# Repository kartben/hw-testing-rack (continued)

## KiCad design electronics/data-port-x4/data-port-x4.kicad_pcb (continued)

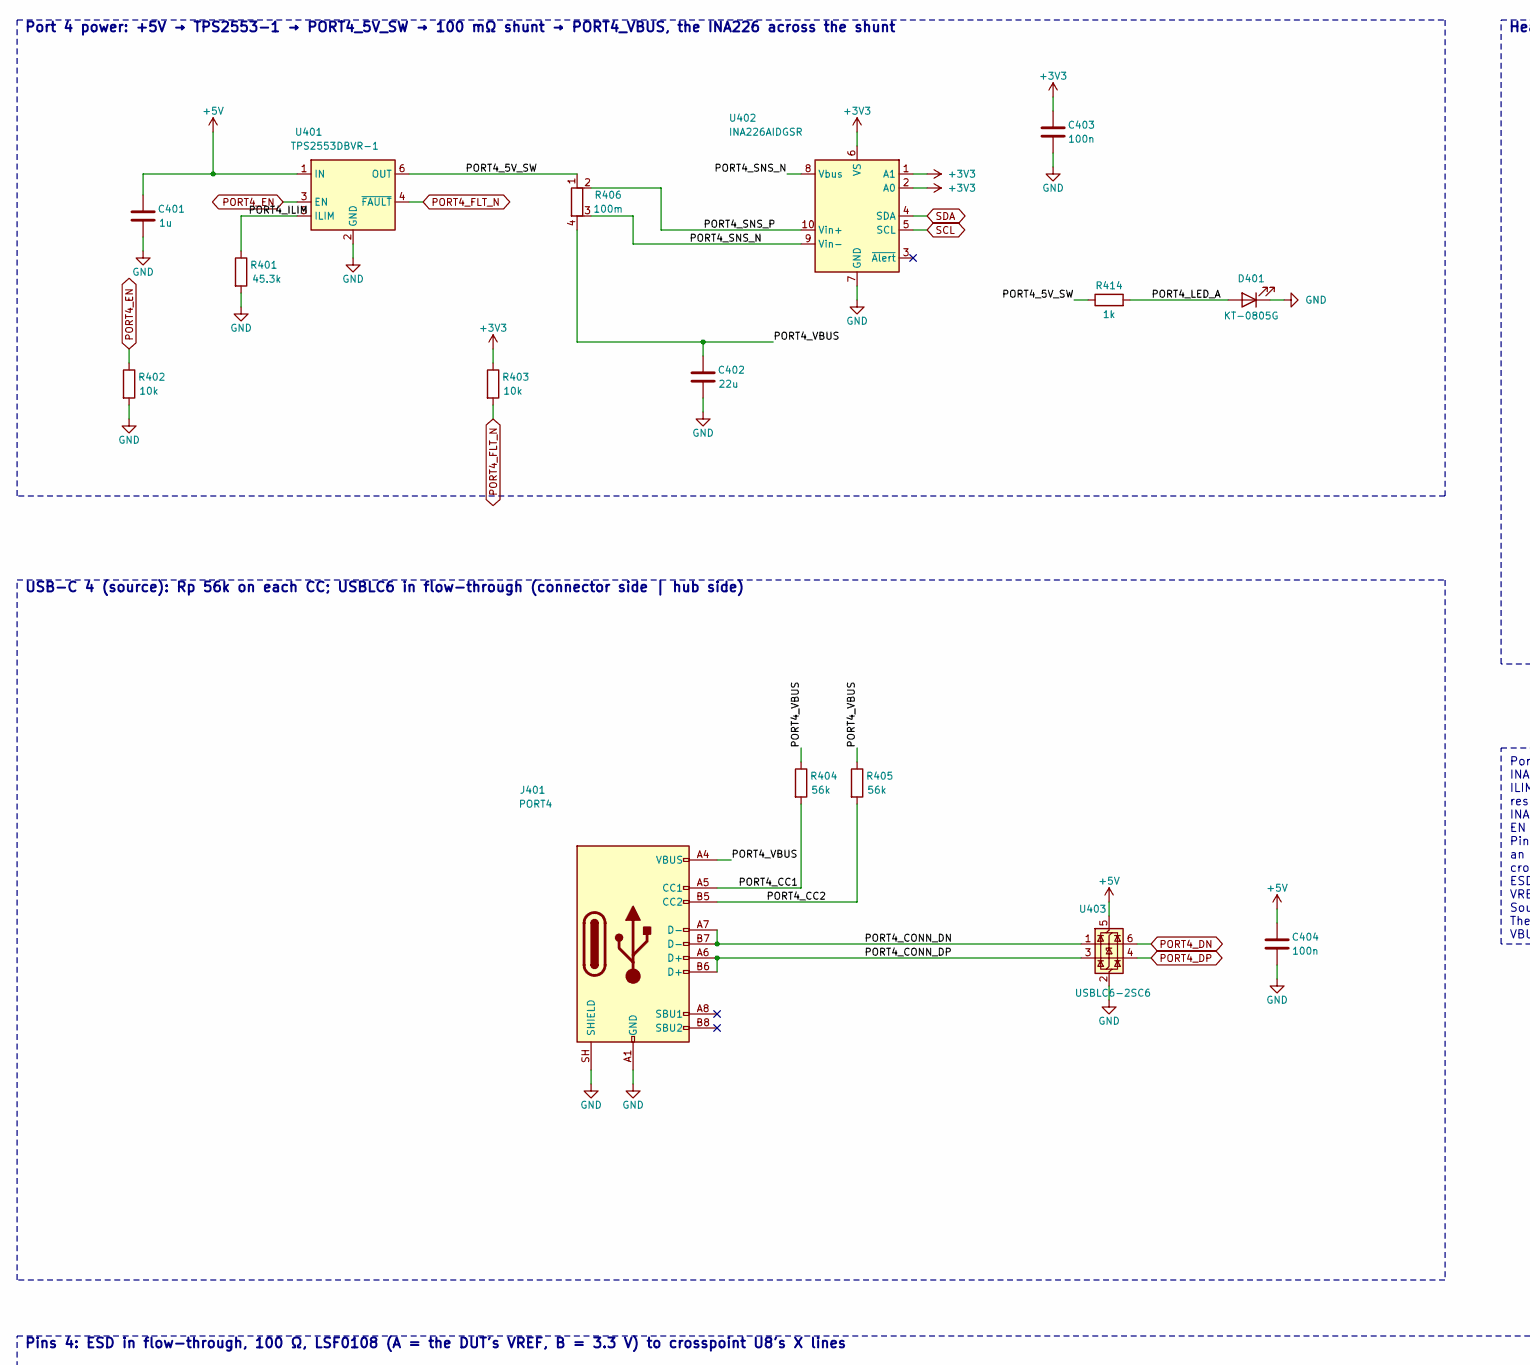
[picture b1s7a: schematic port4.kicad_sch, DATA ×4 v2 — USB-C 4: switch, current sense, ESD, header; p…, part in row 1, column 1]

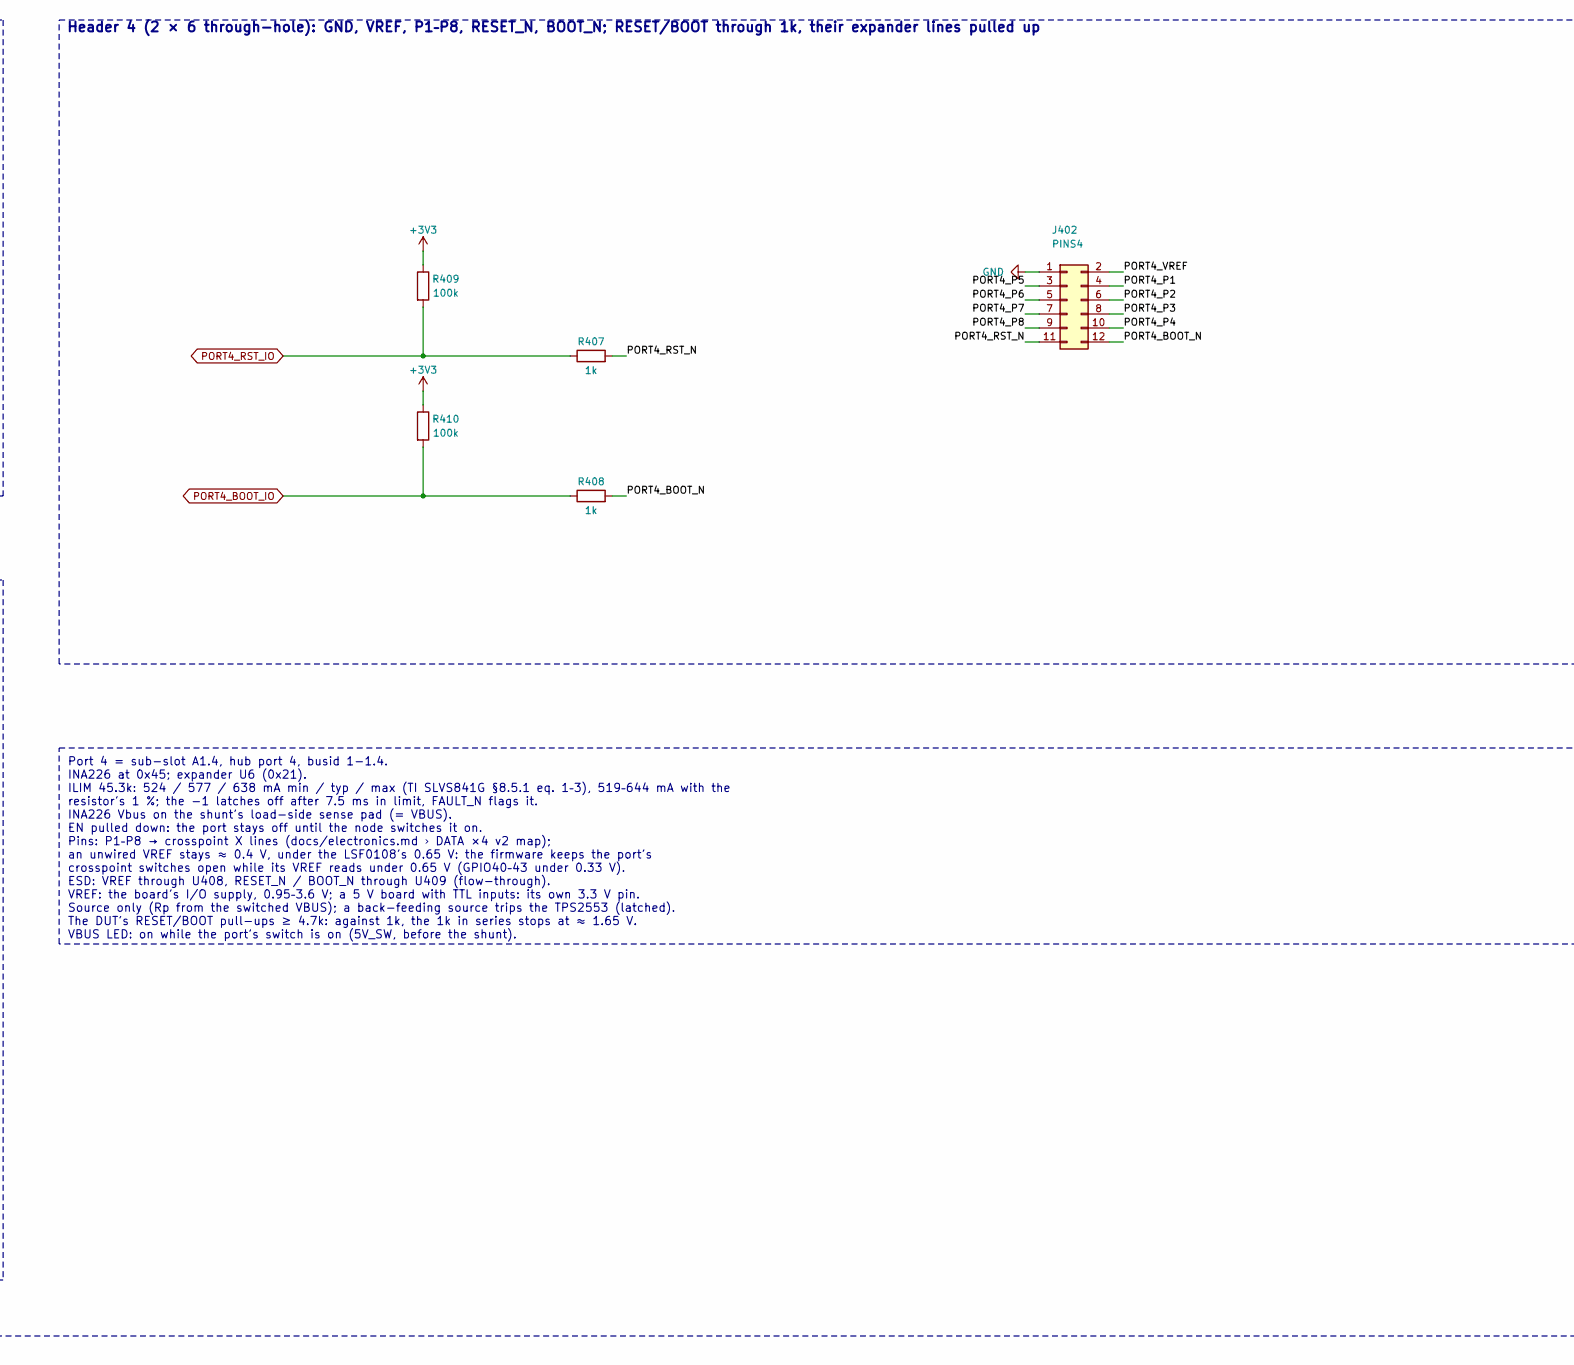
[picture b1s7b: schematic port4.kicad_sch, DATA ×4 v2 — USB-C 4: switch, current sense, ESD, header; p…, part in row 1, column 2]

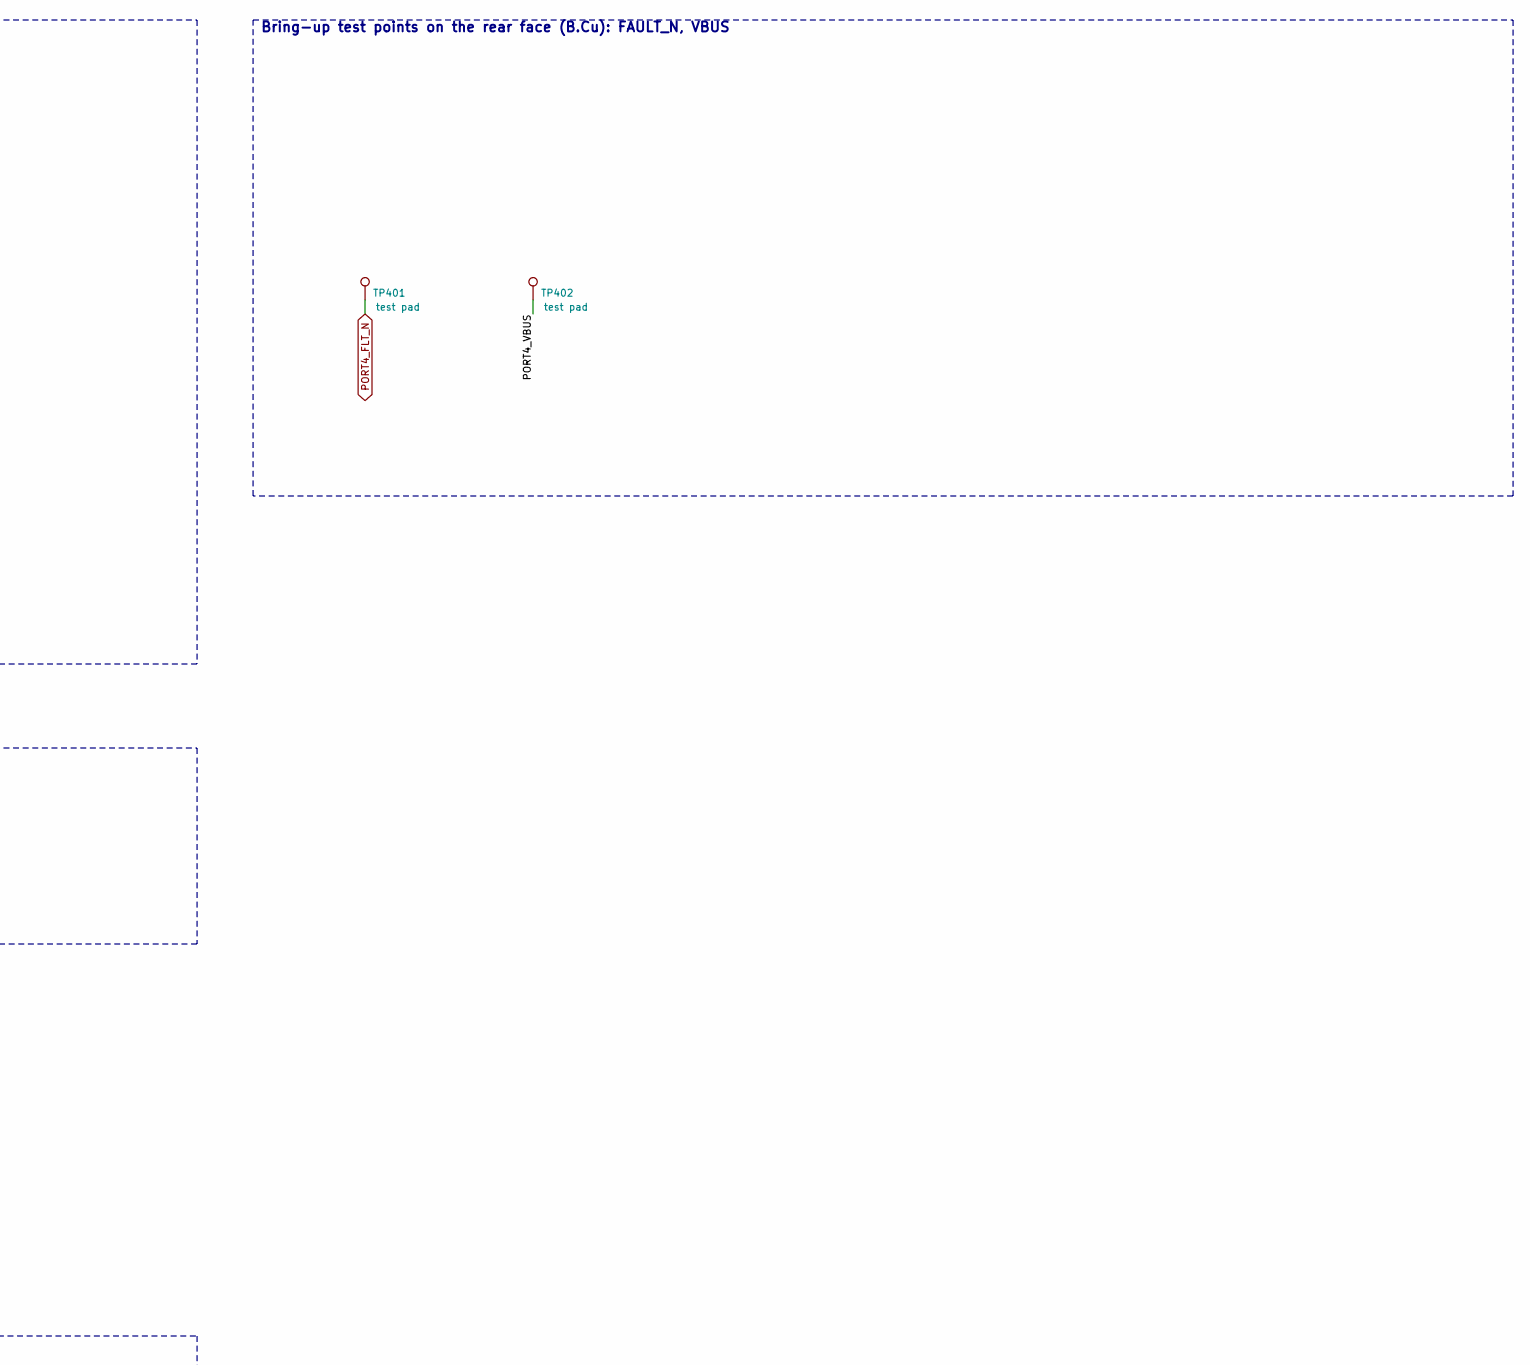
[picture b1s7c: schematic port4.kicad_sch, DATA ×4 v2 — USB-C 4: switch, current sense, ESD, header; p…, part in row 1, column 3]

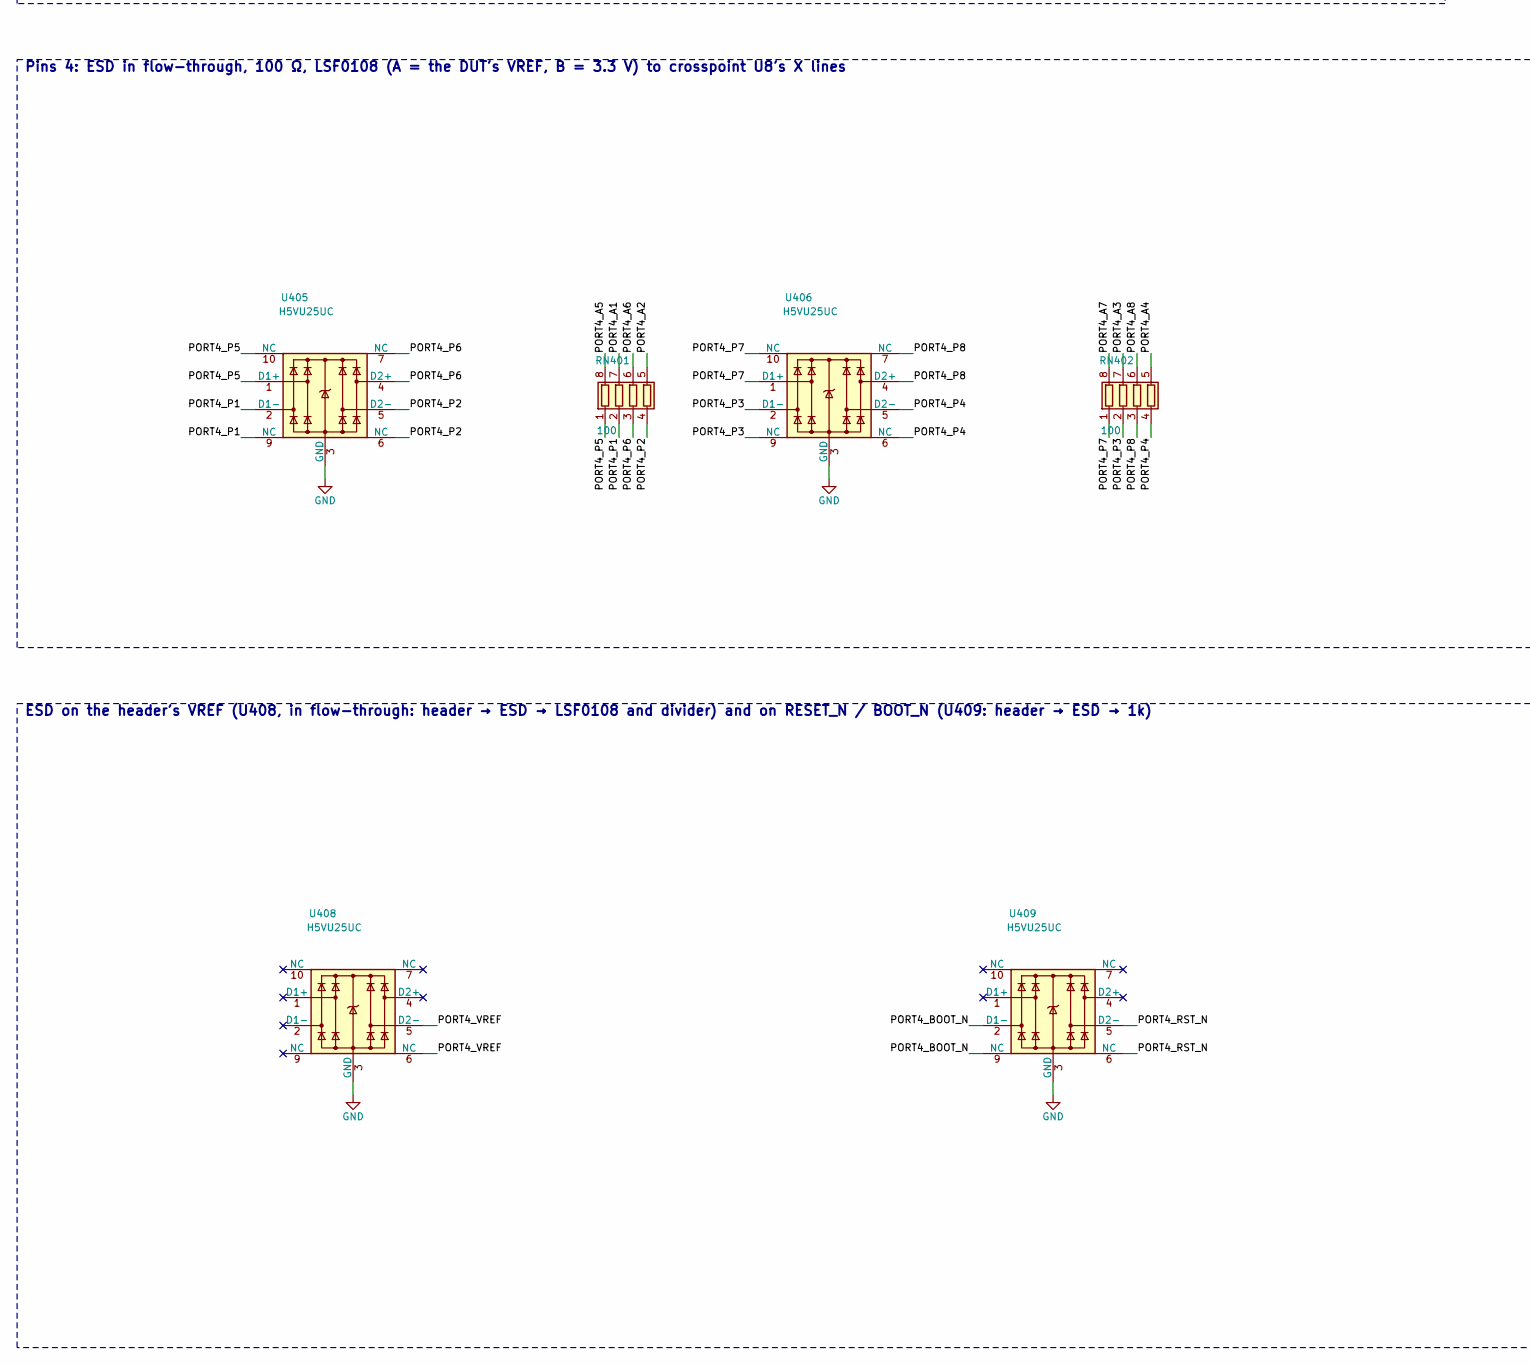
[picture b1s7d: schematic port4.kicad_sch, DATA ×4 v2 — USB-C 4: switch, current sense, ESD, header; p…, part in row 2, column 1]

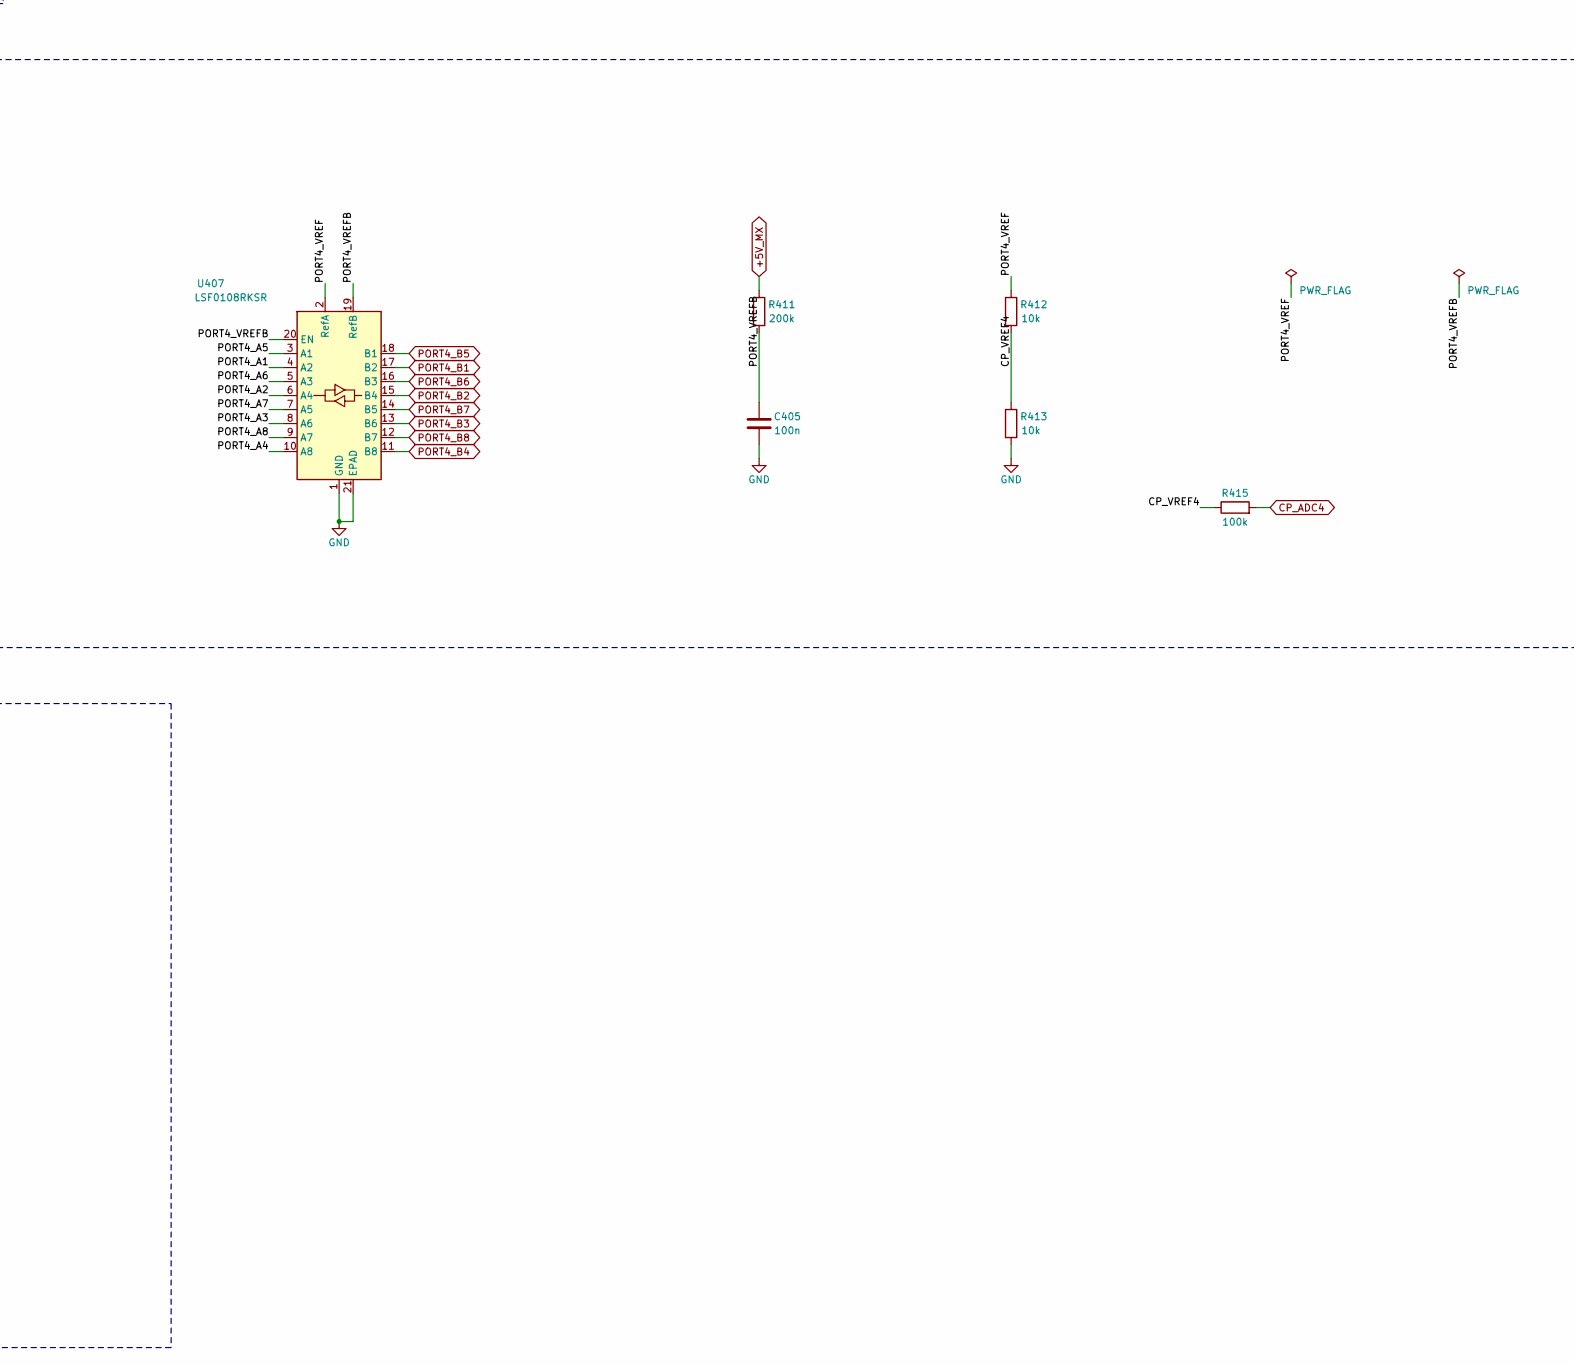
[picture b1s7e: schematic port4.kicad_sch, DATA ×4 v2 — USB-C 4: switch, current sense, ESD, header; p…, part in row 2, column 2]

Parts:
C401: 1u; C_0402_1005Metric; MPN CL05A105KA5NQNC; LCSC C52923
C402: 22u; C_0805_2012Metric; MPN CL21A226MAQNNNE; LCSC C45783
C403, C404, C405: 100n; C_0402_1005Metric; MPN CL05B104KO5NNNC; LCSC C1525
D401: KT-0805G; LED_0805_2012Metric; MPN KT-0805G; LCSC C2297
J401: PORT4; USB_C_Receptacle_GCT_USB4145-03-0170-C_Vertical; MPN USB4145-03-0170-C; LCSC C5181332
J402: PINS4; PinHeader_2x06_P2.54mm_Vertical; MPN HX PZ2.54-2x6P ZZ; LCSC C32713279
R401: 45.3k; R_0402_1005Metric; MPN FRC0402F4532TS; LCSC C2933099
R402, R403, R412, R413: 10k; R_0402_1005Metric; MPN 0402WGF1002TCE; LCSC C25744
R404, R405: 56k; R_0402_1005Metric; MPN 0402WGF5602TCE; LCSC C25796
R406: 100m; R_1206_3216Metric_Kelvin; MPN 1206W4F100LT5E; LCSC C25334
R407, R408, R414: 1k; R_0402_1005Metric; MPN 0402WGF1001TCE; LCSC C11702
R409, R410, R415: 100k; R_0402_1005Metric; MPN 0402WGF1003TCE; LCSC C25741
R411: 200k; R_0402_1005Metric; MPN 0402WGF2003TCE; LCSC C25764
RN401, RN402: 100; R_Array_Convex_4x0402; MPN 4D02WGJ0101TCE; LCSC C48442
TP401: test pad; TestPoint_Pad_D1.0mm; MPN test pad
TP402: test pad; TestPoint_Pad_D1.5mm; MPN test pad
U401: TPS2553DBVR-1; SOT-23-6; MPN TPS2553DBVR-1; LCSC C111738
U402: INA226AIDGSR; TSSOP-10_3x3mm_P0.5mm; MPN INA226AIDGSR; LCSC C49851
U403: USBLC6-2SC6; SOT-23-6; MPN USBLC6-2SC6; LCSC C7519
U405, U406, U408, U409: H5VU25UC; DFN2510-10L_2.5x1.0mm_P0.5mm; MPN H5VU25UC; LCSC C20615800
U407: LSF0108RKSR; DHVQFN-20-1EP_2.5x4.5mm_P0.5mm_EP1x3mm; MPN LSF0108RKSR; LCSC C130008

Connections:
+3V3: C403.1, R403.1, R409.1, R410.1, U402.1 (A1), U402.2 (A0), U402.6 (VS); also elsewhere on the board
+5V: C401.1, C404.1, U401.1 (IN), U403.5 (VBUS); also elsewhere on the board
+5V_MX: R411.1; also elsewhere on the board
/Port 4/CP_VREF4: R412.2, R413.1, R415.1
/Port 4/PORT4_5V_SW: R406.1, R414.1, U401.6 (OUT)
/Port 4/PORT4_A1: RN401.7 (R2.2), U407.4 (A2)
/Port 4/PORT4_A2: RN401.5 (R4.2), U407.6 (A4)
/Port 4/PORT4_A3: RN402.7 (R2.2), U407.8 (A6)
/Port 4/PORT4_A4: RN402.5 (R4.2), U407.10 (A8)
/Port 4/PORT4_A5: RN401.8 (R1.2), U407.3 (A1)
/Port 4/PORT4_A6: RN401.6 (R3.2), U407.5 (A3)
/Port 4/PORT4_A7: RN402.8 (R1.2), U407.7 (A5)
/Port 4/PORT4_A8: RN402.6 (R3.2), U407.9 (A7)
/Port 4/PORT4_BOOT_N: J402.12, R408.2, U409.2 (D1-), U409.9 (NC)
/Port 4/PORT4_CC1: J401.A5 (CC1), R404.2
/Port 4/PORT4_CC2: J401.B5 (CC2), R405.2
/Port 4/PORT4_CONN_DN: J401.A7 (D-), J401.B7 (D-), U403.1 (I/O1)
/Port 4/PORT4_CONN_DP: J401.A6 (D+), J401.B6 (D+), U403.3 (I/O2)
/Port 4/PORT4_ILIM: R401.1, U401.5 (ILIM)
/Port 4/PORT4_LED_A: D401.2 (A), R414.2
/Port 4/PORT4_P1: J402.4, RN401.2 (R2.1), U405.2 (D1-), U405.9 (NC)
/Port 4/PORT4_P2: J402.6, RN401.4 (R4.1), U405.5 (D2-), U405.6 (NC)
/Port 4/PORT4_P3: J402.8, RN402.2 (R2.1), U406.2 (D1-), U406.9 (NC)
/Port 4/PORT4_P4: J402.10, RN402.4 (R4.1), U406.5 (D2-), U406.6 (NC)
/Port 4/PORT4_P5: J402.3, RN401.1 (R1.1), U405.1 (D1+), U405.10 (NC)
/Port 4/PORT4_P6: J402.5, RN401.3 (R3.1), U405.4 (D2+), U405.7 (NC)
/Port 4/PORT4_P7: J402.7, RN402.1 (R1.1), U406.1 (D1+), U406.10 (NC)
/Port 4/PORT4_P8: J402.9, RN402.3 (R3.1), U406.4 (D2+), U406.7 (NC)
/Port 4/PORT4_RST_N: J402.11, R407.2, U409.5 (D2-), U409.6 (NC)
/Port 4/PORT4_SNS_N: R406.3, U402.8 (Vbus), U402.9 (Vin-)
/Port 4/PORT4_SNS_P: R406.2, U402.10 (Vin+)
/Port 4/PORT4_VBUS: C402.1, J401.A4 (VBUS), J401.A9 (VBUS), J401.B4 (VBUS), J401.B9 (VBUS), R404.1, R405.1, R406.4, TP402.1
/Port 4/PORT4_VREF: J402.2, R412.1, U407.2 (RefA), U408.5 (D2-), U408.6 (NC)
/Port 4/PORT4_VREFB: C405.1, R411.2, U407.19 (RefB), U407.20 (EN)
CP_ADC4: R415.2; also elsewhere on the board
GND: C401.2, C402.2, C403.2, C404.2, C405.2, D401.1 (K), J401.A1 (GND), J401.A12 (GND), J401.B1 (GND), J401.B12 (GND), J401.SH (SHIELD), J402.1, R401.2, R402.2, R413.2, U401.2 (GND), U402.7 (GND), U403.2 (GND), U405.3 (GND), U405.8 (GND), U406.3 (GND), U406.8 (GND), U407.1 (GND), U407.21 (EPAD), U408.3 (GND), U408.8 (GND), U409.3 (GND), U409.8 (GND); also elsewhere on the board
PORT4_B1: U407.17 (B2); also elsewhere on the board
PORT4_B2: U407.15 (B4); also elsewhere on the board
PORT4_B3: U407.13 (B6); also elsewhere on the board
PORT4_B4: U407.11 (B8); also elsewhere on the board
PORT4_B5: U407.18 (B1); also elsewhere on the board
PORT4_B6: U407.16 (B3); also elsewhere on the board
PORT4_B7: U407.14 (B5); also elsewhere on the board
PORT4_B8: U407.12 (B7); also elsewhere on the board
PORT4_BOOT_IO: R408.1, R410.2; also elsewhere on the board
PORT4_DN: U403.6 (I/O1); also elsewhere on the board
PORT4_DP: U403.4 (I/O2); also elsewhere on the board
PORT4_EN: R402.1, U401.3 (EN); also elsewhere on the board
PORT4_FLT_N: R403.2, TP401.1, U401.4 (~FAULT); also elsewhere on the board
PORT4_RST_IO: R407.1, R409.2; also elsewhere on the board
SCL: U402.5 (SCL); also elsewhere on the board
SDA: U402.4 (SDA); also elsewhere on the board

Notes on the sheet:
Port 4 power: +5V → TPS2553-1 → PORT4_5V_SW → 100 mΩ shunt → PORT4_VBUS, the INA226 across the shunt
Bring-up test points on the rear face (B.Cu): FAULT_N, VBUS
USB-C 4 (source): Rp 56k on each CC; USBLC6 in flow-through (connector side | hub side)
Header 4 (2 × 6 through-hole): GND, VREF, P1–P8, RESET_N, BOOT_N; RESET/BOOT through 1k, their expander lines pulled up
ESD on the header's VREF (U408, in flow-through: header → ESD → LSF0108 and divider) and on RESET_N / BOOT_N (U409: header → ESD → 1k)
Pins 4: ESD in flow-through, 100 Ω, LSF0108 (A = the DUT's VREF, B = 3.3 V) to crosspoint U8's X lines
Port 4 = sub-slot A1.4, hub port 4, busid 1-1.4. INA226 at 0x45; expander U6 (0x21). ILIM 45.3k: 524 / 577 / 638 mA min / typ / max (TI SLVS841G §8.5.1 eq. 1–3), 519–644 mA with the resistor's 1 %; the -1 latches off after 7.5 ms in limit, FAULT_N flags it. INA226 Vbus on the shunt's load-side sens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

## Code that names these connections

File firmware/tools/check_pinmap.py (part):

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        "dts": ["bay_node_procpu.dts", "bay_node.dtsi", "bay_node-pinctrl.dtsi"],
        "nets": {
            "BOOT": ("gpio", "gpios"),
            "PC_DET": ("gpio", "pc-detect-gpios"),
            "SVC": ("gpio", "service-gpios"),
            "DUT_EN": ("gpio", "enable-gpios"),
            "DUT_FLT_N": ("gpio", "fault-gpios"),
            "MUX_FORCE_PC": ("gpio", "force-pc-gpios"),
            "AUX_RST_CTL": ("gpio", "reset-gpios"),
            "AUX_BOOT_CTL": ("gpio", "boot-gpios"),
            "INA_ALERT_N": ("gpio", "alert-gpios"),
            "I2C_SDA": ("pinmux", "I2C0_SDA"),
            "I2C_SCL": ("pinmux", "I2C0_SCL"),
            "LED_DIN": ("pinmux", "RMT_OUT0"),
            "AUX_TX": ("pinmux", "UART1_TX"),
            "AUX_RX": ("pinmux", "UART1_RX"),
            "U0TX": ("pinmux", "UART0_TX"),
            "U0RX": ("pinmux", "UART0_RX"),
            "CAN_TXD": ("pinmux", "TWAI_TX"),
            "CAN_RXD": ("pinmux", "TWAI_RX"),
            "POS_IN": ("gpio", "pos-in-gpios"),
            "POS_OUT": ("gpio", "pos-out-gpios"),
            "CAM_SCK": ("pinmux", "SPIM2_SCLK"),
            "CAM_MOSI": ("pinmux", "SPIM2_MOSI"),
            "CAM_MISO": ("pinmux", "SPIM2_MISO"),
            "CAM_CS": ("gpio", "cs-gpios"),
            "CAM_LED": ("pinmux", "LEDC_CH0"),
        },
        # Nets that also appear a second way
        "also": {"AUX_TX": [("gpio", "tx-gpios")]},  # dut-port: the TX pin as a GPIO
        # Nets on fixed-function pins: nothing to check in the devicetree
        "fixed": {"ESP_DN", "ESP_DP"},  # IO19/IO20, the internal USB PHY (&usb_otg)
        # Nets wired on the board that no devicetree node uses yet (README says so): skipped
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            "BOOT": ("gpio", "gpios", "boot_button"),
            **{f"ADC_IMON_{r}": ("adc", f"imon_{r.lower()}") for r in "ABCD"},
            "VBUS_SENSE": ("adc", "vbus_sense"),
            "CAN_TXD": ("pinmux", "TWAI_TX"),
            "CAN_RXD": ("pinmux", "TWAI_RX"),
            "CAN_STB": ("gpio", "standby-gpios", "can_phy"),
            **{f"POS_{r}": ("gpio", "pos-gpios", f"row_{r.lower()}") for r in "ABCD"},
            **{f"ROW_EN_{r}": ("gpio", "enable-gpios", f"row_{r.lower()}") for r in "ABCD"},
            **{f"FLT_{r}": ("gpio", "fault-gpios", f"row_{r.lower()}") for r in "ABCD"},
            "CTL_LED": ("gpio", "gpios", "ctl_led"),
            "PD_INT": ("gpio", "pg-gpios", "pd_sink"),
            "PD_SCL": ("pinmux", "I2C0_SCL"),
            "PD_SDA": ("pinmux", "I2C0_SDA"),
            "I2C_PU": ("gpio", "i2c-pullup-gpios", "power_hub"),
            "U0TX": ("pinmux", "UART0_TX"),
            "U0RX": ("pinmux", "UART0_RX"),
        },
        "also": {},
        "fixed": {"USB_DN", "USB_DP"},  # IO19/IO20: the console USB-C (USB-Serial-JTAG)
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
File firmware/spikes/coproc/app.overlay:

/*
 * DATA ×4 v2 co-processor spike on a Pico 2 (README.md).  Pins follow the
 * v2 research: the eight buses are GPIO2-9 (CH1-8).
 *
 *   GPIO2-9   sampled by the PIO capture (all eight)
 *   GPIO4/5   I2C0 target: an emulated TMP103 at 0x70 (CH3/CH4)
 *   GPIO6/7   I2C1 target: an emulated 256-byte EEPROM at 0x50 (CH5/CH6)
 *   GPIO8/9   UART1, bridged to the "con1" CDC-ACM port (CH7/CH8)
 *
 * SPDX-License-Identifier: Apache-2.0
 */

/ {
	chosen {
		zephyr,shell-uart = &cdc_acm_shell;
	};

	/* A DUT console: UART1 <-> USB, line coding passed through */
	uart-bridge-con1 {
		compatible = "zephyr,uart-bridge";
		peers = <&cdc_acm_con1 &uart1>;
	};
};

&zephyr_udc0 {
	cdc_acm_shell: cdc_acm_shell {
		compatible = "zephyr,cdc-acm-uart";
		label = "coproc shell";
	};

	cdc_acm_con1: cdc_acm_con1 {
		compatible = "zephyr,cdc-acm-uart";
		label = "coproc con1";
	};

	/* con2/con3: for PIO UARTs, which have no interrupt API yet (README.md) */
	cdc_acm_con2: cdc_acm_con2 {
		compatible = "zephyr,cdc-acm-uart";
		label = "coproc con2";
	};

	cdc_acm_con3: cdc_acm_con3 {
		compatible = "zephyr,cdc-acm-uart";
		label = "coproc con3";
	};
};

&pinctrl {
	uart1_bus: uart1_bus {
		group1 {
			pinmux = <UART1_TX_P8>;
		};

		group2 {
			pinmux = <UART1_RX_P9>;
			input-enable;
		};
	};
};

&uart1 {
	current-speed = <115200>;
	pinctrl-0 = <&uart1_bus>;
	pinctrl-names = "default";
	status = "okay";
};

/* The board's defaults already put I2C0 on GPIO4/5 and I2C1 on GPIO6/7 */
&i2c0 {
	tmp103_emul: tmp103@70 {
		compatible = "zephyr,i2c-target-tmp103";
		reg = <0x70>;
		sensor = <&die_temp>;
	};
};

&i2c1 {
	eeprom_emul: eeprom@50 {
		compatible = "zephyr,i2c-target-eeprom";
		reg = <0x50>;
		size = <256>;
	};
};

&adc {
	status = "okay";
};

&die_temp {
	status = "okay";
};

/* Own labels: the pico-sdk headers define pio0 (and friends) as macros */
coproc_pio: &pio0 {
	status = "okay";
};

coproc_dma: &dma {
	status = "okay";
};

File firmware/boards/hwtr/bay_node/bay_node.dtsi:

/*
 * Bay node peripherals, shared by the board definition and by the
 * esp32s3_devkitc stand-in overlay (firmware/bay-node/boards/).
 *
 * Source of truth: electronics/bay-node/design.py.  Keep the pin table in
 * firmware/README.md in sync with this file.
 *
 * SPDX-License-Identifier: Apache-2.0
 */

#include <zephyr/dt-bindings/gpio/gpio.h>
#include <zephyr/dt-bindings/i2c/i2c.h>
#include <zephyr/dt-bindings/led/led.h>
#include <zephyr/dt-bindings/pwm/pwm.h>

/ {
	aliases {
		led-strip = &status_led;
	};

	/*
	 * The camera's light: a few white 5 V LEDs on the pod, switched low-side
	 * on LED_K.  25 kHz: slow PWM bands a rolling shutter.
	 */
	camera_light: camera-light {
		compatible = "pwm-leds";

		camera_light_led: light {
			label = "camera light";
			pwms = <&ledc0 0 PWM_KHZ(25) PWM_POLARITY_NORMAL>;
		};
	};

	dut_port: dut-port {
		compatible = "hwtr,dut-port";
		/* IO41 DUT_EN -> TPS26600 SHDN (U9, 10k pull-down: DATA_VIN off without firmware) */
		enable-gpios = <&gpio1 9 GPIO_ACTIVE_HIGH>;
		/* IO40 DUT_FLT_N <- 1k (R43) <- TPS26600 ~FLT (10k pull-up): low in a fault, and while off or ramping */
		fault-gpios = <&gpio1 8 (GPIO_ACTIVE_LOW | GPIO_PULL_UP)>;
		vin-efuse;
		/* IO1 SCL, IO2 SDA: read before DATA_VIN goes on (the DATA lead's power-on rule) */
		bus-gpios = <&gpio0 1 GPIO_ACTIVE_HIGH>, <&gpio0 2 GPIO_ACTIVE_HIGH>;
		/* IO12 AUX_RST_CTL / IO48 AUX_BOOT_CTL -> 2N7002 gates (100k pull-downs) */
		reset-gpios = <&gpio0 12 GPIO_ACTIVE_HIGH>;
		boot-gpios = <&gpio1 16 GPIO_ACTIVE_HIGH>;
		power-monitor = <&ina226>;
		uart = <&uart1>;
		/* IO47 AUX_TX as a GPIO: released while the DUT is off, low for a BREAK */
		tx-gpios = <&gpio1 15 GPIO_ACTIVE_HIGH>;
	};

	usb_mux: usb-mux {
		compatible = "hwtr,usb-mux";
		/* IO14 MUX_FORCE_PC -> OR gate (100k pull-down) */
		force-pc-gpios = <&gpio0 14 GPIO_ACTIVE_HIGH>;
		/* IO13 PC_DET <- front port VBUS, 10k/20k divider */
		pc-detect-gpios = <&gpio0 13 (GPIO_ACTIVE_HIGH | GPIO_PULL_DOWN)>;
		/* IO15 SVC <- SERVICE slide switch */
		service-gpios = <&gpio0 15 (GPIO_ACTIVE_HIGH | GPIO_PULL_DOWN)>;
	};

	/* Rack bus (docs/can.md): CAN on the row cable, and the POS addressing token */
	rack_bus: rack-bus {
		compatible = "hwtr,rack-bus";
		/* IO16 POS_IN <- J1.6 through 10k and a BAT54S clamp, 150k pull-down */
		pos-in-gpios = <&gpio0 16 GPIO_ACTIVE_HIGH>;
		/* IO42 POS_OUT -> J2.1 (J2 is J1 mirrored) through 10k and a BAT54S clamp: low until the node has an address */
		pos-out-gpios = <&gpio1 10 GPIO_ACTIVE_HIGH>;
		can = <&twai>;
	};

	status_led: ws2812 {
		compatible = "worldsemi,ws2812-pulse-io";
		pulse-ios = <&rmt 0>;
		chain-length = <1>;
		color-mapping = <LED_COLOR_ID_GREEN
				 LED_COLOR_ID_RED
				 LED_COLOR_ID_BLUE>;
		reset-delay = <300>;
	};
};

&gpio0 {
	status = "okay";
};

&gpio1 {
	status = "okay";
};

&uart1 {
	status = "okay";
	current-speed = <115200>;
	pinctrl-0 = <&bay_aux_uart_default>;
	pinctrl-names = "default";
};

/*
 * 100 kHz: the bus goes out on the DATA lead (J7, 45 cm) to the DATA board,
 * through its isolation FETs; 400 kHz is out of reach on rise time there.
 * firmware/bay-node/i2c-400k.overlay tries 400 kHz at bring-up.
 */
&i2c0 {
	status = "okay";
	clock-frequency = <I2C_BITRATE_STANDARD>;
	pinctrl-0 = <&bay_i2c0_default>;
	pinctrl-names = "default";

	/*
	 * U10, A0 = A1 = GND; 50 mOhm shunt R19 on DATA_VIN, after the eFuse
	 * -> 81.92 mV / 50 mOhm = 1.64 A full scale
	 */
	ina226: ina226@40 {
		compatible = "ti,ina226";
		reg = <0x40>;
		current-lsb-microamps = <50>;
		rshunt-micro-ohms = <50000>;
		/* 4 averages: 8.8 ms a reading, the ALERT that sheds a DATA x4 port */
		avg-count = <4>;
		/* IO39 INA_ALERT_N (10k pull-up): src/ports.c sets it and takes its interrupt */
		alert-gpios = <&gpio1 7 GPIO_ACTIVE_LOW>;
	};
};

/* IO18/IO17: TWAI on the TJA1462AT (U11, VIO 3.3 V, STB tied low on the board) */
&twai {
	status = "okay";
	pinctrl-0 = <&bay_twai_default>;
	pinctrl-names = "default";
	bitrate = <250000>;
};

&rmt {
	status = "okay";
	pinctrl-0 = <&bay_led_default>;
	pinctrl-names = "default";
};

/* IO19/IO20: the internal full-speed PHY, wired to MUX_DUT (DUT) and MUX_PC (SERVICE) */
zephyr_uhc0: &usb_otg {
	status = "okay";
};

&wifi {
	status = "okay";
};

&ledc0 {
	pinctrl-0 = <&bay_ledc0_default>;
	pinctrl-names = "default";
	status = "okay";
	#address-cells = <1>;
	#size-cells = <0>;

	channel0@0 {
		reg = <0x0>;
		timer = <0>;
	};
};

/*
 * J6: the bay camera, an Arducam Mega on a ~50 cm lead: SPI mode 0 at 4 MHz
 * (2 MHz if the lead misbehaves).  No DMA: the CPU copies into the frame
 * buffer in PSRAM.  Optional: without a camera its driver fails to start
 * and the node runs on, the API says "no camera".
 */
&spi2 {
	#address-cells = <1>;
	#size-cells = <0>;
	status = "okay";
	pinctrl-0 = <&bay_spim2_default>;
	pinctrl-names = "default";
	cs-gpios = <&gpio0 4 GPIO_ACTIVE_LOW>;

	camera: camera@0 {
		compatible = "arducam,mega";
		reg = <0>;
		spi-max-frequency = <4000000>;
	};
};
